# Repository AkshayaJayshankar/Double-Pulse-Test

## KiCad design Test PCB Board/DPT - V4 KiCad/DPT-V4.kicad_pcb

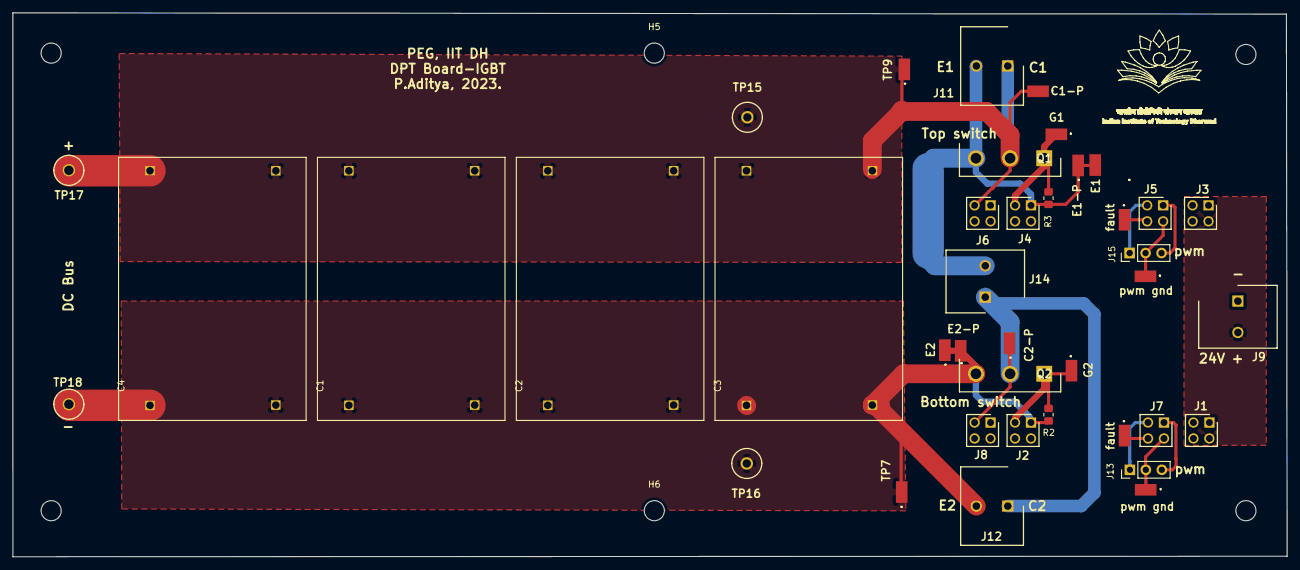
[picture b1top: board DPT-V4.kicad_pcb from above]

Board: 2 copper layers, 202.9 x 86.6 mm, 46 parts (0 on the bottom side), 16 nets.

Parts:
C1, C2, C3, C4: EZP-V80406MTS; cap
C1-P, C2-P: S1751-46R; S175146R
E1, E1-P, E2, E2-P: S1751-46R; S175146R
G1, G2: S1751-46R; S175146R
H1, H2, H3, H4, H5, H6: MountingHole; MountingHole_3.2mm_M3
J1, J2, J3, J4, J5, J6, J7, J8: 90151-2104; RHDR4W64P254_2X2_493X498X870P
J9, J11, J12, J14: 796690-2; SHDR2W101P0X500_1X2_1000X1250X1500P
J13, J15: Conn_01x03_Male; PinHeader_1x03_P2.54mm_Vertical
Q1, Q2: IKW15N120H3; TO544P521X1592X2557-3P
R2, R3: R; R_0805_2012Metric_Pad1.20x1.40mm_HandSolder
TP7, TP9: S1751-46R; S175146R
TP15, TP16, TP17, TP18: 105-2210-201; 1052210201
fault: S1751-46R; S175146R
fault#2: S1751-46R; S175146R
pwm gnd: S1751-46R; S175146R
pwm gnd#2: S1751-46R; S175146R

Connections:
Desat: C2-P.1, J8.3, J12.1, J14.1, Q2.2
Desat-1: C1.1, C1.3, C1-P.1, C2.1, C2.3, C3.1, C3.3, C4.1, C4.3, J6.3, J11.1, Q1.2, TP9.1, TP15.1, TP17.1
E1: E1.1, E1-P.1, J4.1, J11.2, J14.2, Q1.3, R3.2
E2: C1.2, C1.4, C2.2, C2.4, C3.2, C3.4, C4.2, C4.4, E2.1, E2-P.1, J2.1, J12.2, Q2.3, R2.2, TP7.1, TP16.1, TP18.1
G1: G1.1, J4.3, Q1.1, R3.1
G2: G2.1, J2.3, Q2.1, R2.1
GND: J1.3, J1.4, J3.3, J3.4, J9.1
GND1: J5.2, J15.2, pwm gnd#2.1
GND2: J7.2, J13.2, pwm gnd.1
Pulse: J7.1, J13.3
Pulse-1: J5.1, J15.3
Vcc: J5.3, J15.1
Vcc1: J7.3, J13.1
Vin: J1.1, J1.2, J3.1, J3.2, J9.2
fault: J7.4, fault.1
fault-1: J5.4, fault#2.1

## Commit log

2026-06-24 added IGBT datasheet
2026-06-24 updated references
2026-06-24 updated PCB boards
2026-06-24 added code
2026-06-24 update PCB
2026-06-24 code update
2026-06-24 Updated Results
2026-06-25 Updated hardware results and board images
    Hardware results updated for 400V and 250V with 38uH inductor. Board images updated.
